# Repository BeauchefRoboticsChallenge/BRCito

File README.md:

# BRCito 2022

[![CC BY NC SA 4.0][cc-by-nc-sa-shield]][cc-by-nc-sa]

Robot velocista sigue-líneas desarrollado para BRC 2022.

El objetivo de este robot es servir de referencia y plataforma para apoyar la formación de los competidores. Está desarrollado en base a las tecnologías disponibles en un FabLab (impresión 3D, fresado de PCBs, Arduino) y comprende las componentes más básicas para funcionar de acuerdo a las reglas de la competencia.

Para poder entregar robots a los colegios participantes de la liga **Sub18** recibimos auspicio de [PCBWay](https://www.pcbway.com/) quienes nos otorgaron las placas electrónicas.

## Diseño

### Antecedentes

Las funciones principales requeridas por el robot son:

- Distinguir una línea blanca en un fondo blanco
- Moverse lo más rápido posible, sin salirse de la pista

Para cumplir estas funciones, el robot requiere una construcción óptima en cuanto al tamaño/peso y las prestaciones de sus componentes que cumplirán estas funcionalidades. El diseño del robot puede seguir diferentes configuraciones (arreglos de sensores, motores, baterías, etc), dependiendo del tipo de control que se vaya a utilizar. Otras funciones secundarias corresponden a la interacción con el usuario (encender/apagar, activar, indicar acciones), así como cualquier otra que se desee agregar (como comunicación inalámbrica para el debugging).

En el contexto de la competencia, existirán marcadores a los costados del circuito que indicarán hitos como curvas, inicio y fin de la pista. También se fija el tamaño máximo como 25x25x20 centímetros (largo, ancho y alto) y que las ruedas no pueden contener elementos adherentes que dañen la pista.

### BRCito Negro PCBWay

El robot sigue líneas es controlador por un Arduino Nano. Las conexiones del Arduino con los sensores, necesarias para realizar su programación se pueden ver en la tabla

#### Pinout electrónico
| Pin Arduino     | Descripción     | Componente | Pin componente
| :------------- | :------------- | :-------      | :-----  |
| A2       | Sensor Frontal 1      | Arreglo sensores QTR-8A | 6
| A3       | Sensor Frontal 2      | Arreglo sensores QTR-8A |5
| A4       | Sensor Frontal 3      | Arreglo sensores QTR-8A |4
| A5       | Sensor Frontal 4      | Arreglo sensores QTR-8A |3
| A6       | Sensor Frontal 5      | Arreglo sensores QTR-8A |2
| A7       | Sensor Frontal 6      | Arreglo sensores QTR-8A |1
| 6        | Rueda izquierda PWM      | Driver motor TB6612FNG | PWMA
| 13       | Rueda izquierda A      | Driver motor TB6612FNG  | AI1 |
| 10       | Rueda izquierda B      | Driver motor TB6612FNG | AI2  |
| 5        | Rueda derecha PWM      | Driver motor TB6612FNG | PWMB |
| 11       | Rueda derecha A      | Driver motor TB6612FNG  | BI1 |
| 12       | Rueda derecha B      | Driver motor TB6612FNG | BI2  |
| A1       | Sensor derecho      | Sensor QTR-1A | out
| A0       | Sensor izquierdo      | Sensor QTR-1A | out
| 9       | Leds RGB      | Led RGB | din led
| 7       | Pulsador      | Pulsador | pin pulsador

### Librerías de Kicad

En la carpeta [pcb/libs/](pcb/libs/) se encuentran las librerías de símbolos y footprints diseñados para los componentes que no existen en las librerías estandar de KiCad.

**Librería de símbolos**
* TB6612FNG_breakout

**Librería de footprints**
* QTR-8
* SPST Slide Switch (interruptor)
* TB6612FNG Breakout

## Librerías de Arduino

Para comunicarse con los leds WS2812b se puede utilizar la librería [Adafruit Neopixel](https://github.com/adafruit/Adafruit_NeoPixel).

Para los sensores infrarrojos QTR se puede utilizar la librería [QTR Sensors](https://github.com/pololu/qtr-sensors-arduino).

## Licencia
[![CC BY NC SA 4.0][cc-by-nc-sa-image]][cc-by-nc-sa]

Este trabajo esta publicado bajo la licencia [Creative Commons Attribution-NonCommercial-ShareAlike 4.0 International
License][cc-by-nc-sa].

Si deseas utilizar nuestro robot en tus proyectos o si te interesa vender las placas, contáctanos y conversemos :)

[cc-by-nc-sa]: https://creativecommons.org/licenses/by-nc-sa/4.0/
[cc-by-nc-sa-image]: https://i.creativecommons.org/l/by-nc-sa/4.0/88x31.png
[cc-by-nc-sa-shield]: https://img.shields.io/badge/License-CC%20BY%20NC%20SA%204.0-lightgrey.svg

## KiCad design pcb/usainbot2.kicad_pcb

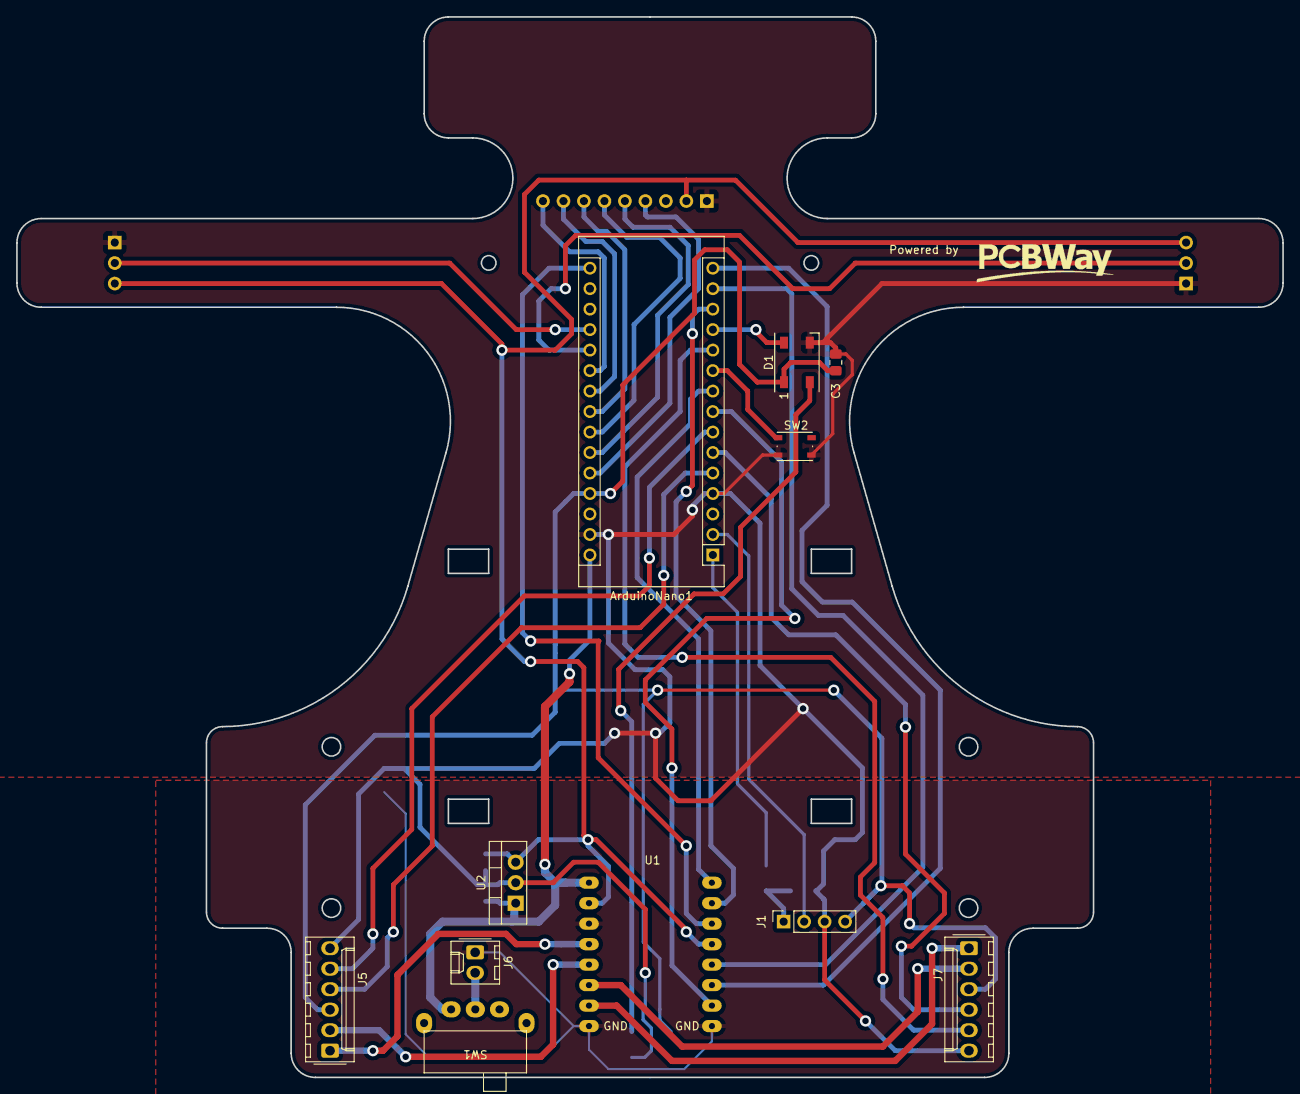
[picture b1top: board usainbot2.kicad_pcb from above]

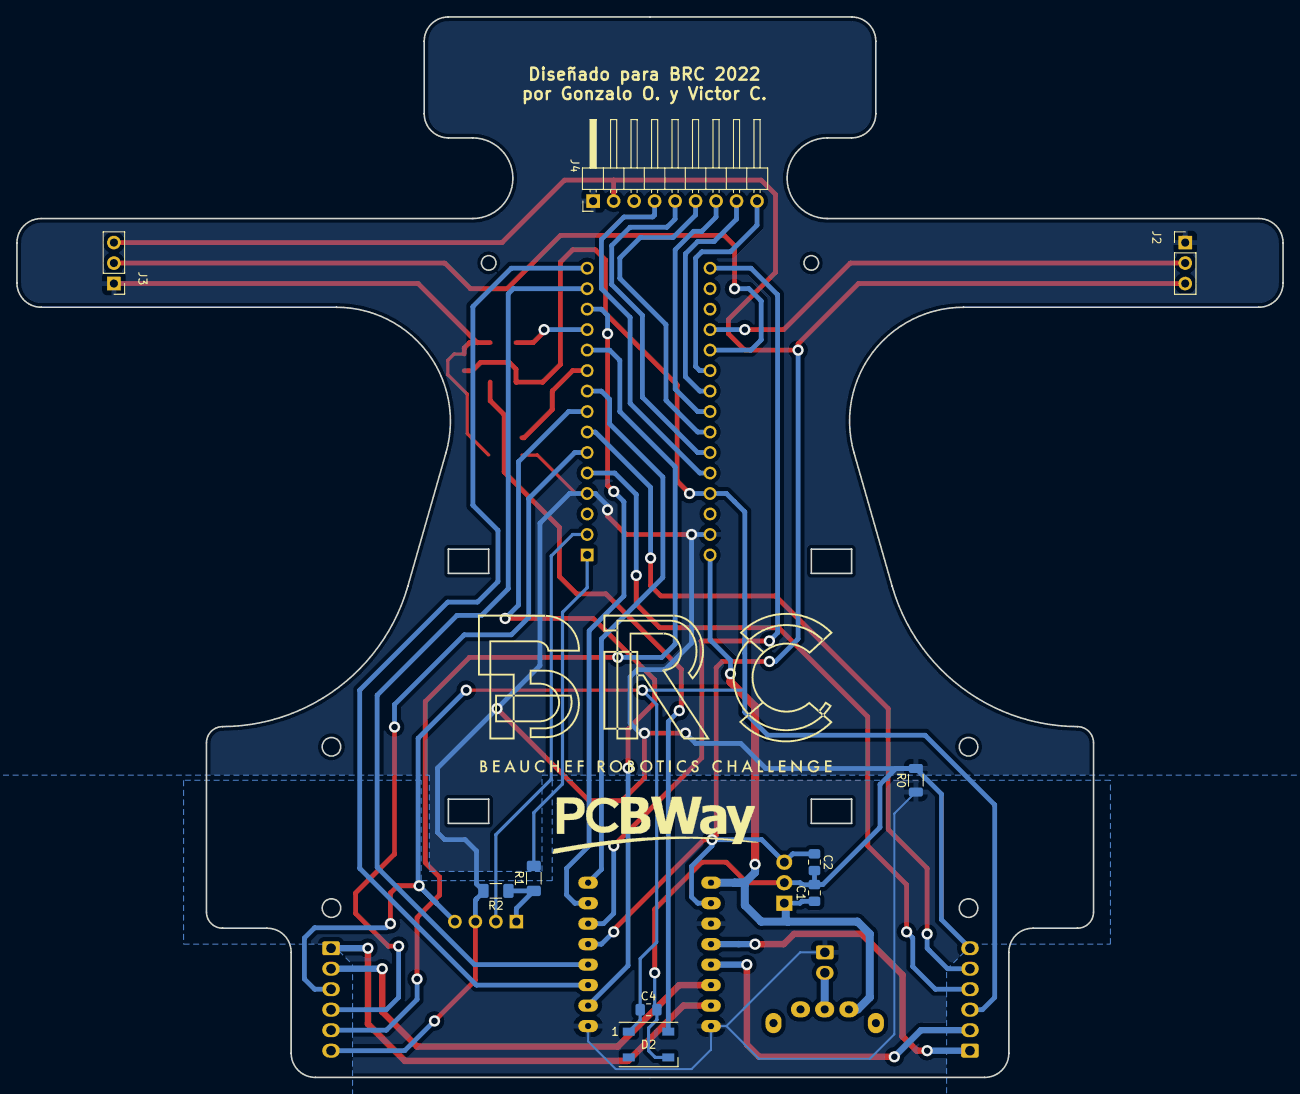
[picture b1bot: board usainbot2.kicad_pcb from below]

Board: 2 copper layers, 157.0 x 131.5 mm, 21 parts (10 on the bottom side), 34 nets.

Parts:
ArduinoNano1: Arduino_Nano_v3.x; Arduino_Nano
C1: 0.22u; C_0805_2012Metric_Pad1.18x1.45mm_HandSolder
C2, C3, C4: 0.1u; C_0805_2012Metric_Pad1.18x1.45mm_HandSolder
D1, D2: WS2812B; LED_WS2812B_PLCC4_5.0x5.0mm_P3.2mm
J1: BT_MOD; PinSocket_1x04_P2.54mm_Vertical
J2: QTR1-L; PinHeader_1x03_P2.54mm_Vertical
J3: QTR1-R; PinHeader_1x03_P2.54mm_Vertical
J4: QTR-6A; PinHeader_1x09_P2.54mm_Horizontal
J5: M1; Molex_KK-254_AE-6410-06A_1x06_P2.54mm_Vertical
J6: BATT; Molex_KK-254_AE-6410-02A_1x02_P2.54mm_Vertical
J7: M2; Molex_KK-254_AE-6410-06A_1x06_P2.54mm_Vertical
R0: RESISTOR1206; R_1206_3216Metric
R1: 1K; R_1206_3216Metric_Pad1.30x1.75mm_HandSolder
R2: 2K; R_1206_3216Metric_Pad1.30x1.75mm_HandSolder
SW1: SW_SPDT; SPST slide switch
SW2: SW_Push; SW_Push_1P1T_NO_Vertical_Wuerth_434133025816
U1: TB6612FNG_breakout; TB6612FNG Breakout
U2: LM7805_TO220; TO-220-3_Vertical

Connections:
+5V: C2.1, J2.3, J3.3, J4.2, U1.2 (VCC), U1.13 (STBY), U2.3 (VO)
+5VD: ArduinoNano1.27 (+5V), C3.1, C4.1, D1.1 (VDD), D2.1 (VDD), J1.4, J5.3, J7.3
/D2: ArduinoNano1.5 (D2), J5.4
/D3: ArduinoNano1.6 (D3), J7.4
/D4: ArduinoNano1.7 (D4), J5.5
/D7: ArduinoNano1.10 (D7), SW2.1
/D8: ArduinoNano1.11 (D8), J7.5
/ML-1: J5.1, U1.4 (AO1)
/ML-2: J5.2, U1.5 (AO2)
/MR-1: J7.1, U1.7 (BO1)
/MR-2: J7.2, U1.6 (BO2)
/QTR-L: ArduinoNano1.19 (A0), J2.2
/QTR-R: ArduinoNano1.20 (A1), J3.2
GND: ArduinoNano1.4 (GND), ArduinoNano1.29 (GND), C1.2, C2.2, C3.2, C4.2, D1.3 (VSS), D2.3 (VSS), J1.3, J2.1, J3.1, J4.1, J5.6, J7.6, R0.2, R2.2, SW2.2, U2.2 (GND)
GNDPWR: J6.1, R0.1, U1.3 (GND), U1.8 (PGND1), U1.9 (PGND2)
unnamed: ArduinoNano1.1 (D1/TX), R1.2
unnamed: ArduinoNano1.2 (D0/RX), J1.2
unnamed: ArduinoNano1.8 (D5), U1.10 (PWMB)
unnamed: ArduinoNano1.9 (D6), U1.16 (PWMA)
unnamed: ArduinoNano1.12 (D9), D1.4 (DIN)
unnamed: ArduinoNano1.13 (D10), U1.15 (AIN2)
unnamed: ArduinoNano1.14 (D11), U1.12 (BIN1)
unnamed: ArduinoNano1.15 (D12), U1.11 (BIN2)
unnamed: ArduinoNano1.16 (D13), U1.14 (AIN1)
unnamed: ArduinoNano1.21 (A2), J4.9
unnamed: ArduinoNano1.22 (A3), J4.8
unnamed: ArduinoNano1.23 (A4), J4.7
unnamed: ArduinoNano1.24 (A5), J4.6
unnamed: ArduinoNano1.25 (A6), J4.5
unnamed: ArduinoNano1.26 (A7), J4.4
unnamed: D1.2 (DOUT), D2.4 (DIN)
unnamed: J1.1, R1.1, R2.1
unnamed: J6.2, SW1.2 (B)
VCC: ArduinoNano1.30 (VIN), C1.1, SW1.3 (C), U1.1 (VM), U2.1 (VI)

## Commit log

2022-08-06 firmware de prueba hw y placa
2022-08-19 actualizado readme con pinout y librerías
2022-09-07 added kicad libraries with switch and tb6612fn
2022-09-21 actualiza el Readme con información de las librerías de kicad
2022-09-23 corrige error de diseño
2022-10-12 se agregan piezas 3d en stl
2023-05-16 update files
2023-05-16 fix deleted

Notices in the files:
pcb/usainbot2.kicad_pcb:
creativecommons.org/licenses/by/4.0
License: CC BY 4.0
